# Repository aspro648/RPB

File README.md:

Rapid Prototyping Board
-------------------------------

What is it?
-----------

- Basically a 32U4 based Arduino with two card-edge slots instead of a shield layout.

Why?
----

- It started out as a 20-pin harness tester (Use Case 1), but morphed into a more generic prototyping system.
- Allows you to quickly prototype systems out on inexpensive small PCBs

Features:
---------

- USB programable Atmega 32U4.
- 20 i/o lines on card 1 position.
- Power, i2c, SPI on both card positions.
- Ability to check what card is plugged in each bay.

License
----------------
[Attribution-ShareAlike 3.0 United States (CC BY-SA 3.0 US)](https://creativecommons.org/licenses/by-sa/3.0/us/)

You are free to:

- Share — copy and redistribute the material in any medium or format
- Adapt — remix, transform, and build upon the material

Under the following terms:

- Attribution — You must give appropriate credit, provide a link to the license, and indicate if changes were made. You may do so in any reasonable manner, but not in any way that suggests the licensor endorses you or your use.
- ShareAlike — If you remix, transform, or build upon the material, you must distribute your contributions under the same license as the original.

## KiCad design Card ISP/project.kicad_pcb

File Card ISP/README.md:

Rapid Prototyping Card - ArduinoISP
---------------------------------------

What is it?
-----------

- Use RPB as an ISP programmer. 
- Sockets for Atmega8/168/328 & Attiny25/24/85.
- ISP jumper for on-board programming.
- D13 (Atmega) and D2 (Attiny) LED for troubleshooting.
- Fused to prevent reversed Attiny meltdown!

Bill Of Materials
----------------
  
- 1 ea., Perfect Purple PCB from OSH Park, https://oshpark.com/shared_projects/yUt0KZ6C
- 2 ea., C1 CAP CER 10UF 10V X5R 0805, Kemet C0805C106K8PAC7800, https://www.digikey.com/short/32v75tfv
- 2 ea., SMD LED GREEN 0603, Lite-On LTST-C191KGKT, https://www.digikey.com/short/ptwhtwz2
- 1 ea., SMD LED RED 0603, Lite-On LTST-C191KRKT, https://www.digikey.com/short/1p9dvv1t
- 1 ea., SMD LED YELLOW 0603, Lite-On LTST-C191KSKT, https://www.digikey.com/short/d20z9t1z
- 1 ea., PTC RESET FUSE 20V 54MA 0805, Murata PRG21AR420MB1RA, https://www.digikey.com/short/2nmhrbvf
- 4 ea., Resistor 1K OHM SMD 0603, Stackpole RNCP0603FTD1K00, https://www.digikey.com/short/704h9hfn
- 1 ea., CONN IC DIP SOCKET 28POS TIN, On Shore ED281DT, https://www.digikey.com/short/d8nq4rd3
- 1 ea., CONN IC DIP SOCKET 8POS, On Shore ED08DT, https://www.digikey.com/short/3tnrjzh5
- 1 ea., 6-PIN SOCKET/SOCKET IDC CABLE, Adafruit 371, https://www.digikey.com/short/b992qfbd
- 1 ea., CONN HEADER VERT 6POS 2.54MM, Amphenol 77313-118-06LF, https://www.digikey.com/short/r2d1pw4f

License
----------------
[Attribution-ShareAlike 3.0 United States (CC BY-SA 3.0 US)](https://creativecommons.org/licenses/by-sa/3.0/us/)

You are free to:

- Share — copy and redistribute the material in any medium or format
- Adapt — remix, transform, and build upon the material

Under the following terms:

- Attribution — You must give appropriate credit, provide a link to the license, and indicate if changes were made. You may do so in any reasonable manner, but not in any way that suggests the licensor endorses you or your use.
- ShareAlike — If you remix, transform, or build upon the material, you must distribute your contributions under the same license as the original.

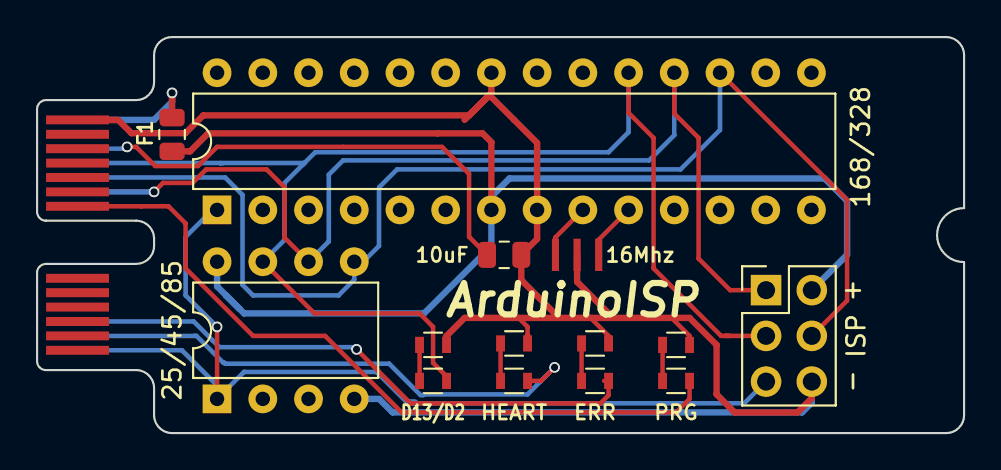
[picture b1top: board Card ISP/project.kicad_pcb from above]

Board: 2 copper layers, 51.5 x 22.0 mm, 15 parts (0 on the bottom side), 17 nets.

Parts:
C1: 10uF; C_0805_2012Metric
D1: HEART; R_0603
D2: ERR; R_0603
D3: PRG; R_0603
D4: D13/D2; R_0603
F1: 54mA; Fuse_0805_2012Metric
J1: ISP; PinHeader_2x03_P2.54mm_Vertical
R1, R2, R3, R4: 1K; R_0603
U1: 25/45/85; DIP-8_W7.62mm
U2: 168/328; DIP-28_W7.62mm
X0: Card Edge; MEC8-113-CARD_2
Y1: 16Mhz; Resonator_SMD_CTSC_1.3mmx3.2mm

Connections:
+5V: F1.2, J1.2, U1.8, U2.7
/LED_ERR: D2.2, X0.3
/LED_HB: D1.2, X0.2
/LED_PMODE: D3.2, X0.20
/MISO: J1.1, U1.6, U2.18, X0.8
/MOSI: J1.4, U1.5, U2.17, X0.9
/RESET: C1.1, X0.11
/RST: J1.5, U1.1, U2.1, X0.1
/SCK: D4.2, J1.3, U1.7, U2.19, X0.10
GND: C1.2, J1.6, R1.1, R2.1, R3.1, R4.1, U1.4, U2.8, U2.22, X0.26, Y1.2
unnamed: D1.1, R2.2
unnamed: D2.1, R3.2
unnamed: D3.1, R4.2
unnamed: D4.1, R1.2
unnamed: F1.1, X0.13
unnamed: U2.9, Y1.3
unnamed: U2.10, Y1.1

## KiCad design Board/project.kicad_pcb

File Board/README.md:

Rapid Prototyping Board
-----------------------

Bill Of Materials
----------------
  
- 1 ea., Perfect Purple PCB from OSH Park, https://oshpark.com/shared_projects/RGBCuiso
- 1 ea., U1 ATMEGA32U4-AU, IC MCU 8BIT 32KB FLASH 44TQFP, https://www.digikey.com/short/jb25pc
- 1 ea., U2 IC CURRENT MONITOR 1% 8SOIC, TI INA219AIDR, https://www.digikey.com/short/z32drn7n
- 1 ea., Y1 CER RES 16.0000MHZ 15PF SMD, Murata CSTNE16M0V530000R0, https://www.digikey.com/short/8nzcmjh3
- 2 ea., C1 CAP CER 10UF 10V X5R 0805, Kemet C0805C106K8PAC7800, https://www.digikey.com/short/32v75tfv
- 1 ea., C2 CAP CER 0.1uF 0603, https://www.digikey.com/short/h3jddqhm 
- 23 ea., D1-D23 SMD LED GREEN 0603, Lite-On LTST-C191KGKT, https://www.digikey.com/short/ptwhtwz2
- 1 ea., F1	PTC RESET FUSE 6V 500MA 0805 Eaton PTS08056V050, https://www.digikey.com/short/4182mdqq
- 2 ea., RV1, RV2 VARISTOR 10.8V 30A 0603, KYOCERA VCUG060050L1DP, https://www.digikey.com/short/0479hw0m
- 23 ea., R1-R23 Resistor 1K OHM SMD 0603, Stackpole RNCP0603FTD1K00, https://www.digikey.com/short/704h9hfn
- 2 ea., R24, R25 Resistor 22 OHM SMD 0603, Yageo RC0603JR-0722RL, https://www.digikey.com/short/93jrm3t2
- 1 ea., R26 Resistor 1M OHM SMD 0603 Yageo RC0603JR-071ML, https://www.digikey.com/short/z0jnrwbq
- 2 ea., R27, R28 Resistor 4K7 OHM SMD 0603, https://www.digikey.com/short/t89ptvpw
- 1 ea., R29 RES 0.1 OHM 1% 1W 1206, VSRP1206S1-R100F, https://www.digikey.com/short/dzw3vt1h
- 2 ea., SW1 SWITCH TACTILE SPST-NO 0.05A 12V, Wurth 434121025816, https://www.digikey.com/short/qbm0p0c9
- 1 ea., J1 CONN RCPT MICRO USB R/A SMD, Molex 1050170001, https://www.digikey.com/short/jb2205
- 2 ea., X1, X2 CONN EDGE DUAL FMALE 20POS, Samtek MEC8-113-02-L-D-RA1, https://www.digikey.com/short/50wdhmp0
- 2 ea., ROUND STANDOFF M2.5 STEEL 2.7MM, Wurth 9774027151R, https://www.digikey.com/short/47zwt3m4
- 1 ea., LED1 3535 RGB LED,  IN-PI33TBTPRPGPB https://www.digikey.com/short/qf2t8bqj
- 4 ea., BUMPER CYLINDRICAL 0.25" DIA CLR, https://www.digikey.com/short/23cbvbh5
- 2 ea., M2.5 thumbscrew https://www.mcmaster.com/99607A263/ or
		 https://www.amazon.com/CNBTR-M2-5x6mm-Knurled-Threaded-Fastener/dp/B07ZJFGGTD

Card:
- 1 ea., RPB Card 2.54mm Pitch, https://oshpark.com/shared_projects/RnMvuNFo
- 1 ea., RES 10K OHM 5% 1/10W 0603, https://www.digikey.com/short/h4w9vtd1
- 1 ea., IC EEPROM 32KBIT I2C, Microchip 24LC32AT-I/MC, https://www.digikey.com/short/r3f225vm
- 1 ea., I2C Display Module 0.91 Inch I2C, https://www.amazon.com/Pieces-Display-Module-SSD1306-Screen/dp/B08N6N8L5Q

Stencil & Jig:
- https://www.oshstencils.com/#invoice/5585b4301f5fdfe7690882e8abfac3aeba5187

License
----------------
[Attribution-ShareAlike 3.0 United States (CC BY-SA 3.0 US)](https://creativecommons.org/licenses/by-sa/3.0/us/)

You are free to:

- Share — copy and redistribute the material in any medium or format
- Adapt — remix, transform, and build upon the material

Under the following terms:

- Attribution — You must give appropriate credit, provide a link to the license, and indicate if changes were made. You may do so in any reasonable manner, but not in any way that suggests the licensor endorses you or your use.
- ShareAlike — If you remix, transform, or build upon the material, you must distribute your contributions under the same license as the original.

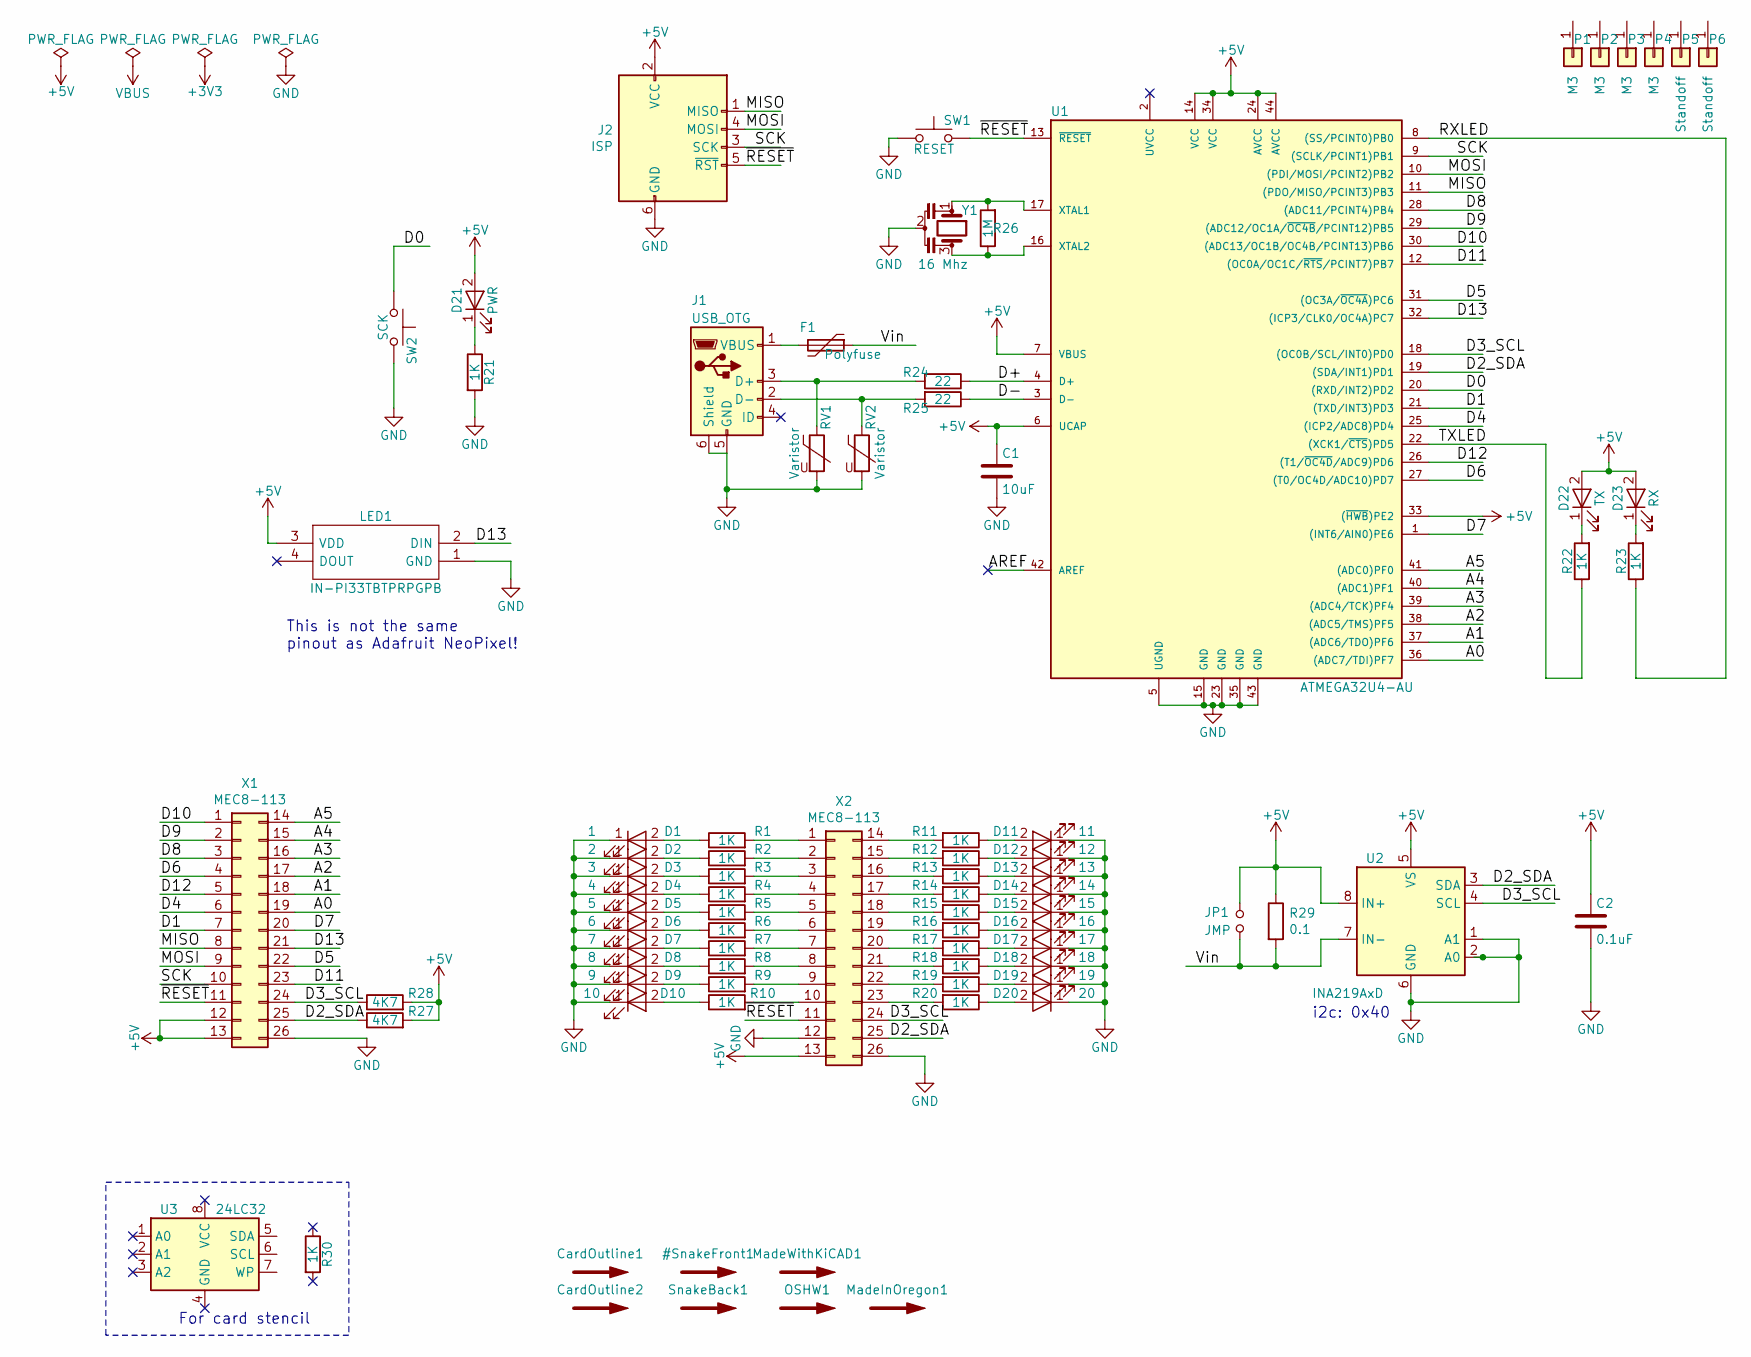
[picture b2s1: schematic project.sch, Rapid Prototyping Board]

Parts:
C1: 10uF; C_0805
C2: 0.1uF; C_0603
CardOutline1, CardOutline2: SYM_Arrow_Large; MEC8-113-CARD_2outline
D1: 1; LED_0603
D2: 2; LED_0603
D3: 3; LED_0603
D4: 4; LED_0603
D5: 5; LED_0603
D6: 6; LED_0603
D7: 7; LED_0603
D8: 8; LED_0603
D9: 9; LED_0603
D10: 10; LED_0603
D11: 11; LED_0603
D12: 12; LED_0603
D13: 13; LED_0603
D14: 14; LED_0603
D15: 15; LED_0603
D16: 16; LED_0603
D17: 17; LED_0603
D18: 18; LED_0603
D19: 19; LED_0603
D20: 20; LED_0603
D21: PWR; LED_0603
D22: TX; LED_0603
D23: RX; LED_0603
F1: Polyfuse; R_0805_HandSoldering
J1: USB_OTG; USB_Micro-B_Molex-105017-0001
J2: ISP; Pin_Header_Straight_2x03_Pitch2.54mm
JP1: JMP; Jumper
LED1: IN-PI33TBTPRPGPB; INPI33TBTPRPGPB; Mouser Part Number 743-IN-PI33TBTPRPGPB
MadeInOregon1: SYM_Arrow_Large; MadeInOregonRev25
MadeWithKiCAD1: SYM_Arrow_Large; KiCad-Logo2_8mm_SilkScreen
OSHW1: SYM_Arrow_Large; OSHW-Logo_11.4x12mm_SilkScreen
P1, P2, P3, P4: M3; M3mount
P5, P6: Standoff; M25standoff
R1, R2, R3, R4, R5, R6, R7, R8, R9, R10, R11, R12, R13, R14, R15, R16, R17, R18, R19, R20, R21, R22, R23, R30: 1K; R_0603
R24, R25: 22; R_0603
R26: 1M; R_0603
R27, R28: 4K7; R_0603
R29: 0.1; R_1206
RV1, RV2: Varistor; R_0603
SW1: RESET; SW_TS10-63-26-BE-250-SMT-TR
SW2: SCK; SW_TS10-63-26-BE-250-SMT-TR
SnakeBack1: SYM_Arrow_Large; Snake
U1: ATMEGA32U4-AU; TQFP-44_10x10mm_Pitch0.8mm
U2: INA219AxD; SOIC-8_3.9x4.9mm_P1.27mm
U3: 24LC32; DFN-8-1EP_3x2mm
X1, X2: MEC8-113; SAMTEC_MEC8-113-TOP-BOTTOM
Y1: 16 Mhz; Resonator_SMD_CTSC_1.3mmx3.2mm

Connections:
+5V: C1.1, C2.1, D21.2 (A), D22.2 (A), D23.2 (A), J2.2 (VCC), JP1.1, LED1.3 (VDD), R27.2, R28.2, R29.1, U1.6 (UCAP), U1.7 (VBUS), U1.14 (VCC), U1.24 (AVCC), U1.33 ((~HWB~)PE2), U1.34 (VCC), U1.44 (AVCC), U2.5 (VS), U2.8 (IN+), X1.12, X1.13, X2.13
/A0: U1.36 ((ADC7/TDI)PF7), X1.19
/A1: U1.37 ((ADC6/TDO)PF6), X1.18
/A2: U1.38 ((ADC5/TMS)PF5), X1.17
/A3: U1.39 ((ADC4/TCK)PF4), X1.16
/A4: U1.40 ((ADC1)PF1), X1.15
/A5: U1.41 ((ADC0)PF0), X1.14
/D0: SW2.1, U1.20 ((RXD/INT2)PD2)
/D1: U1.21 ((TXD/INT3)PD3), X1.7
/D2_SDA: R27.1, U1.19 ((SDA/INT1)PD1), U2.3 (SDA), X1.25, X2.25
/D3_SCL: R28.1, U1.18 ((OC0B/SCL/INT0)PD0), U2.4 (SCL), X1.24, X2.24
/D4: U1.25 ((ICP2/ADC8)PD4), X1.6
/D5: U1.31 ((OC3A/~OC4A~)PC6), X1.22
/D6: U1.27 ((T0/OC4D/ADC10)PD7), X1.4
/D7: U1.1 ((INT6/AIN0)PE6), X1.20
/D8: U1.28 ((ADC11/PCINT4)PB4), X1.3
/D9: U1.29 ((ADC12/OC1A/~OC4B~/PCINT12)PB5), X1.2
/D10: U1.30 ((ADC13/OC1B/OC4B/PCINT13)PB6), X1.1
/D11: U1.12 ((OC0A/OC1C/~RTS~/PCINT7)PB7), X1.23
/D12: U1.26 ((T1/~OC4D~/ADC9)PD6), X1.5
/D13: LED1.2 (DIN), U1.32 ((ICP3/CLK0/OC4A)PC7), X1.21
/D+: R24.1, U1.4 (D+)
/D-: R25.1, U1.3 (D-)
/MISO: J2.1 (MISO), U1.11 ((PDO/MISO/PCINT3)PB3), X1.8
/MOSI: J2.4 (MOSI), U1.10 ((PDI/MOSI/PCINT2)PB2), X1.9
/RXLED: R23.1, U1.8 ((SS/PCINT0)PB0)
/SCK: J2.3 (SCK), U1.9 ((SCLK/PCINT1)PB1), X1.10
/TXLED: R22.1, U1.22 ((XCK1/~CTS~)PD5)
/Vin: F1.1, JP1.2, R29.2, U2.7 (IN-)
/~RESET: J2.5 (~RST), SW1.2, U1.13 (~RESET~), X1.11, X2.11
GND: C1.2, C2.2, D1.1 (K), D2.1 (K), D3.1 (K), D4.1 (K), D5.1 (K), D6.1 (K), D7.1 (K), D8.1 (K), D9.1 (K), D10.1 (K), D11.1 (K), D12.1 (K), D13.1 (K), D14.1 (K), D15.1 (K), D16.1 (K), D17.1 (K), D18.1 (K), D19.1 (K), D20.1 (K), J1.5 (GND), J1.6 (Shield), J2.6 (GND), LED1.1 (GND), R21.2, RV1.2, RV2.2, SW1.1, SW2.2, U1.5 (UGND), U1.15 (GND), U1.23 (GND), U1.35 (GND), U1.43 (GND), U2.1 (A1), U2.2 (A0), U2.6 (GND), X1.26, X2.12, X2.26, Y1.2
unnamed: D1.2 (A), R1.1
unnamed: D2.2 (A), R2.1
unnamed: D3.2 (A), R3.1
unnamed: D4.2 (A), R4.1
unnamed: D5.2 (A), R5.1
unnamed: D6.2 (A), R6.1
unnamed: D7.2 (A), R7.1
unnamed: D8.2 (A), R8.1
unnamed: D9.2 (A), R9.1
unnamed: D10.2 (A), R10.1
unnamed: D11.2 (A), R11.1
unnamed: D12.2 (A), R12.1
unnamed: D13.2 (A), R13.1
unnamed: D14.2 (A), R14.1
unnamed: D15.2 (A), R15.1
unnamed: D16.2 (A), R16.1
unnamed: D17.2 (A), R17.1
unnamed: D18.2 (A), R18.1
unnamed: D19.2 (A), R19.1
unnamed: D20.2 (A), R20.1
unnamed: D21.1 (K), R21.1
unnamed: D22.1 (K), R22.2
unnamed: D23.1 (K), R23.2
unnamed: F1.2, J1.1 (VBUS)
unnamed: J1.2 (D-), R25.2, RV2.1
unnamed: J1.3 (D+), R24.2, RV1.1
unnamed: R1.2, X2.1
unnamed: R2.2, X2.2
unnamed: R3.2, X2.3
unnamed: R4.2, X2.4
unnamed: R5.2, X2.5
unnamed: R6.2, X2.6
unnamed: R7.2, X2.7
unnamed: R8.2, X2.8
unnamed: R9.2, X2.9
unnamed: R10.2, X2.10
unnamed: R11.2, X2.14
unnamed: R12.2, X2.15
unnamed: R13.2, X2.16
unnamed: R14.2, X2.17
unnamed: R15.2, X2.18
unnamed: R16.2, X2.19
unnamed: R17.2, X2.20
unnamed: R18.2, X2.21
unnamed: R19.2, X2.22
unnamed: R20.2, X2.23
unnamed: R26.1, U1.16 (XTAL2), Y1.3
unnamed: R26.2, U1.17 (XTAL1), Y1.1

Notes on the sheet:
This is not the same pinout as Adafruit NeoPixel!
i2c: 0x40
For card stencil

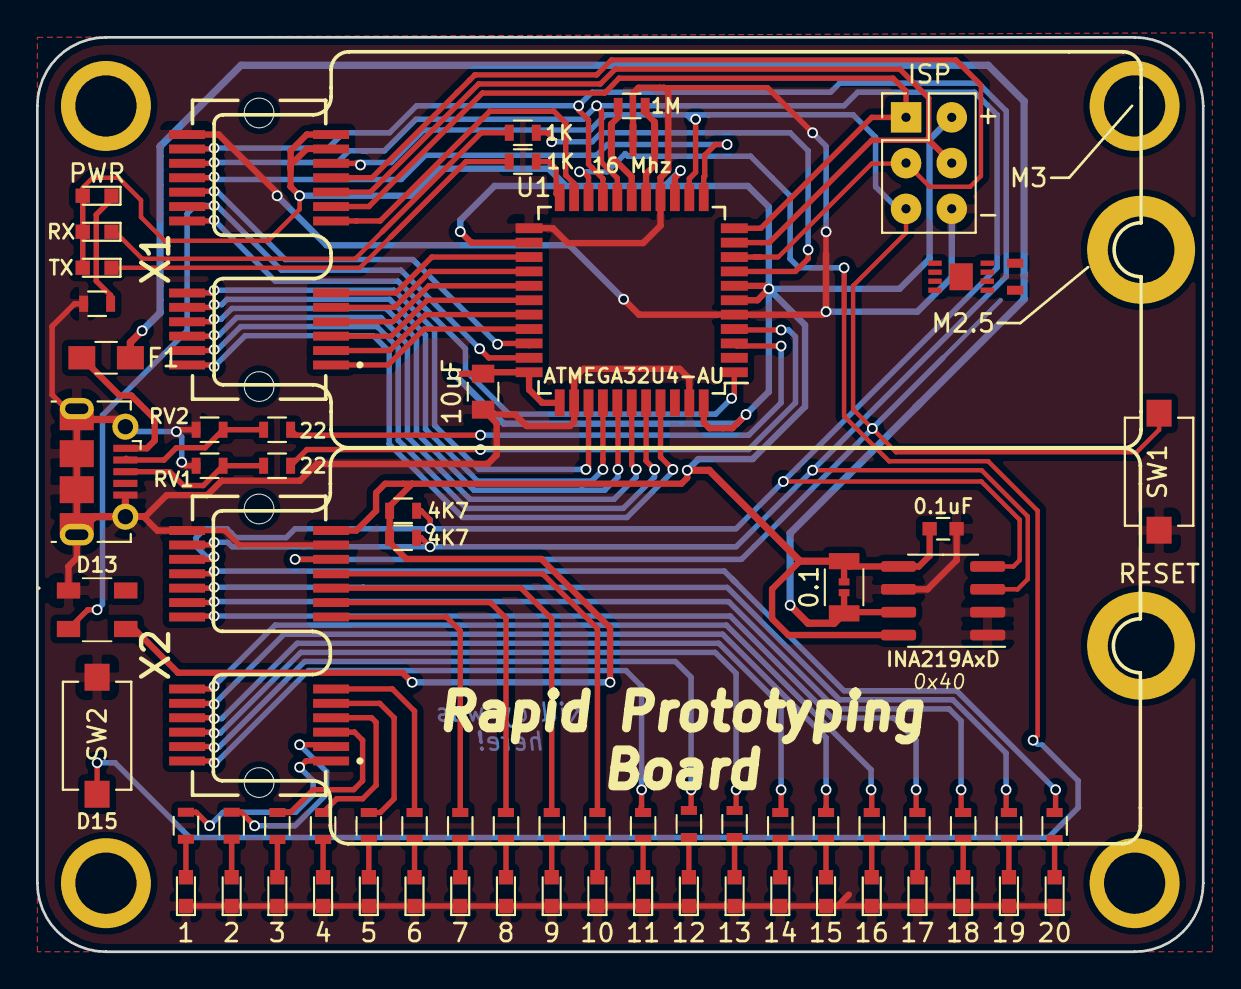
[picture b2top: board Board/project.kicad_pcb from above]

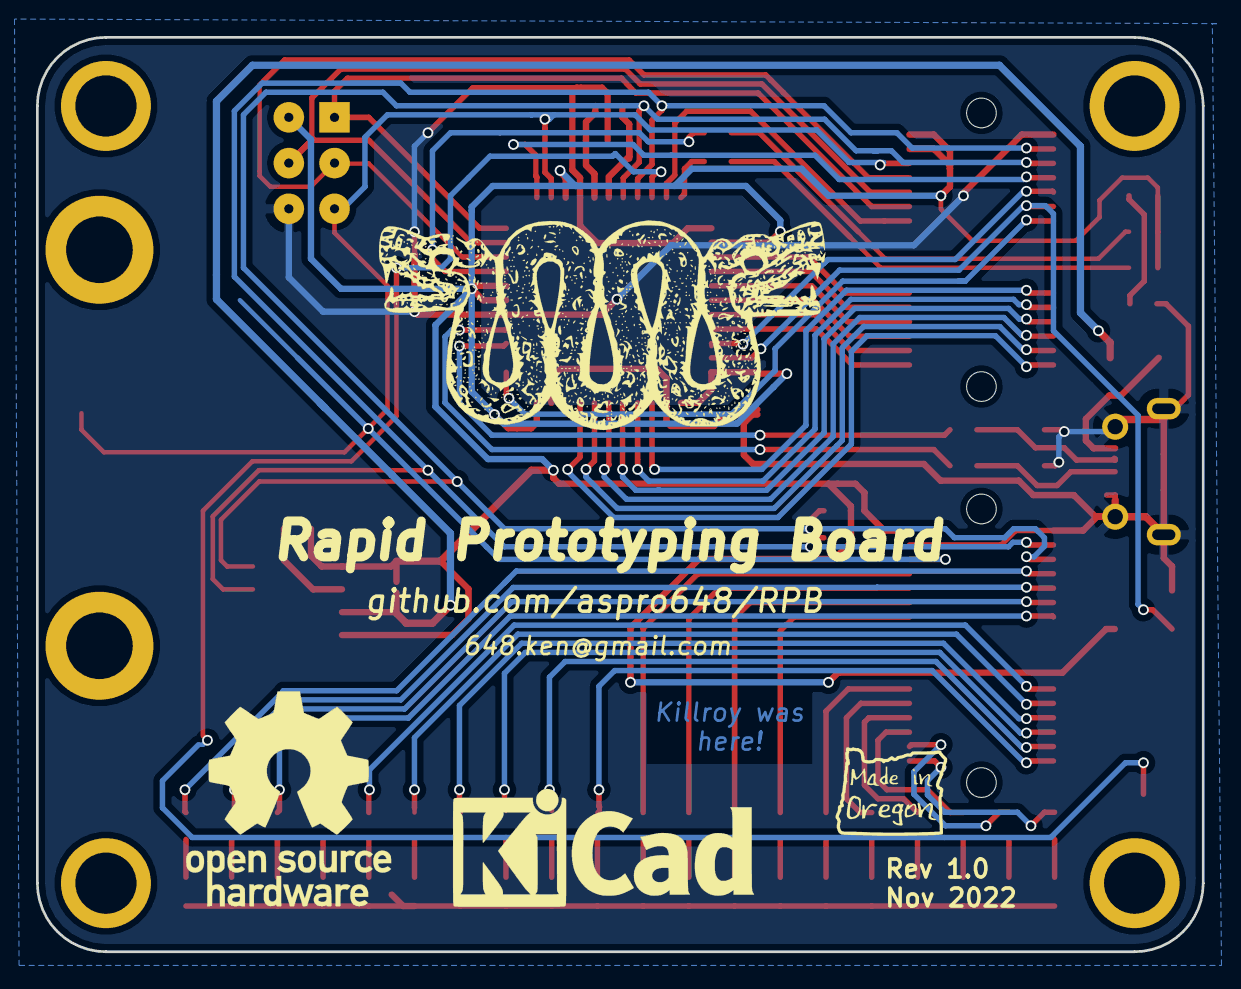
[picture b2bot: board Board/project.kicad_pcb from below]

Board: 2 copper layers, 64.8 x 50.8 mm, 82 parts (3 on the bottom side), 79 nets.

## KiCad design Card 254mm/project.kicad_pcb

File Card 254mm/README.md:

Rapid Prototyping Card - 2.54mm Pitch
-------------------------------------

Bill Of Materials
----------------
  
- PCB from KiCad project.kicad_pcb file  
- 1 ea., RES 10K OHM 5% 1/10W 0603, https://www.digikey.com/short/h4w9vtd1
- 1 ea., IC EEPROM 32KBIT I2C, Microchip 24LC32AT-I/MC, https://www.digikey.com/short/r3f225vm

License
----------------
[Attribution-ShareAlike 3.0 United States (CC BY-SA 3.0 US)](https://creativecommons.org/licenses/by-sa/3.0/us/)

You are free to:

- Share — copy and redistribute the material in any medium or format
- Adapt — remix, transform, and build upon the material

Under the following terms:

- Attribution — You must give appropriate credit, provide a link to the license, and indicate if changes were made. You may do so in any reasonable manner, but not in any way that suggests the licensor endorses you or your use.
- ShareAlike — If you remix, transform, or build upon the material, you must distribute your contributions under the same license as the original.

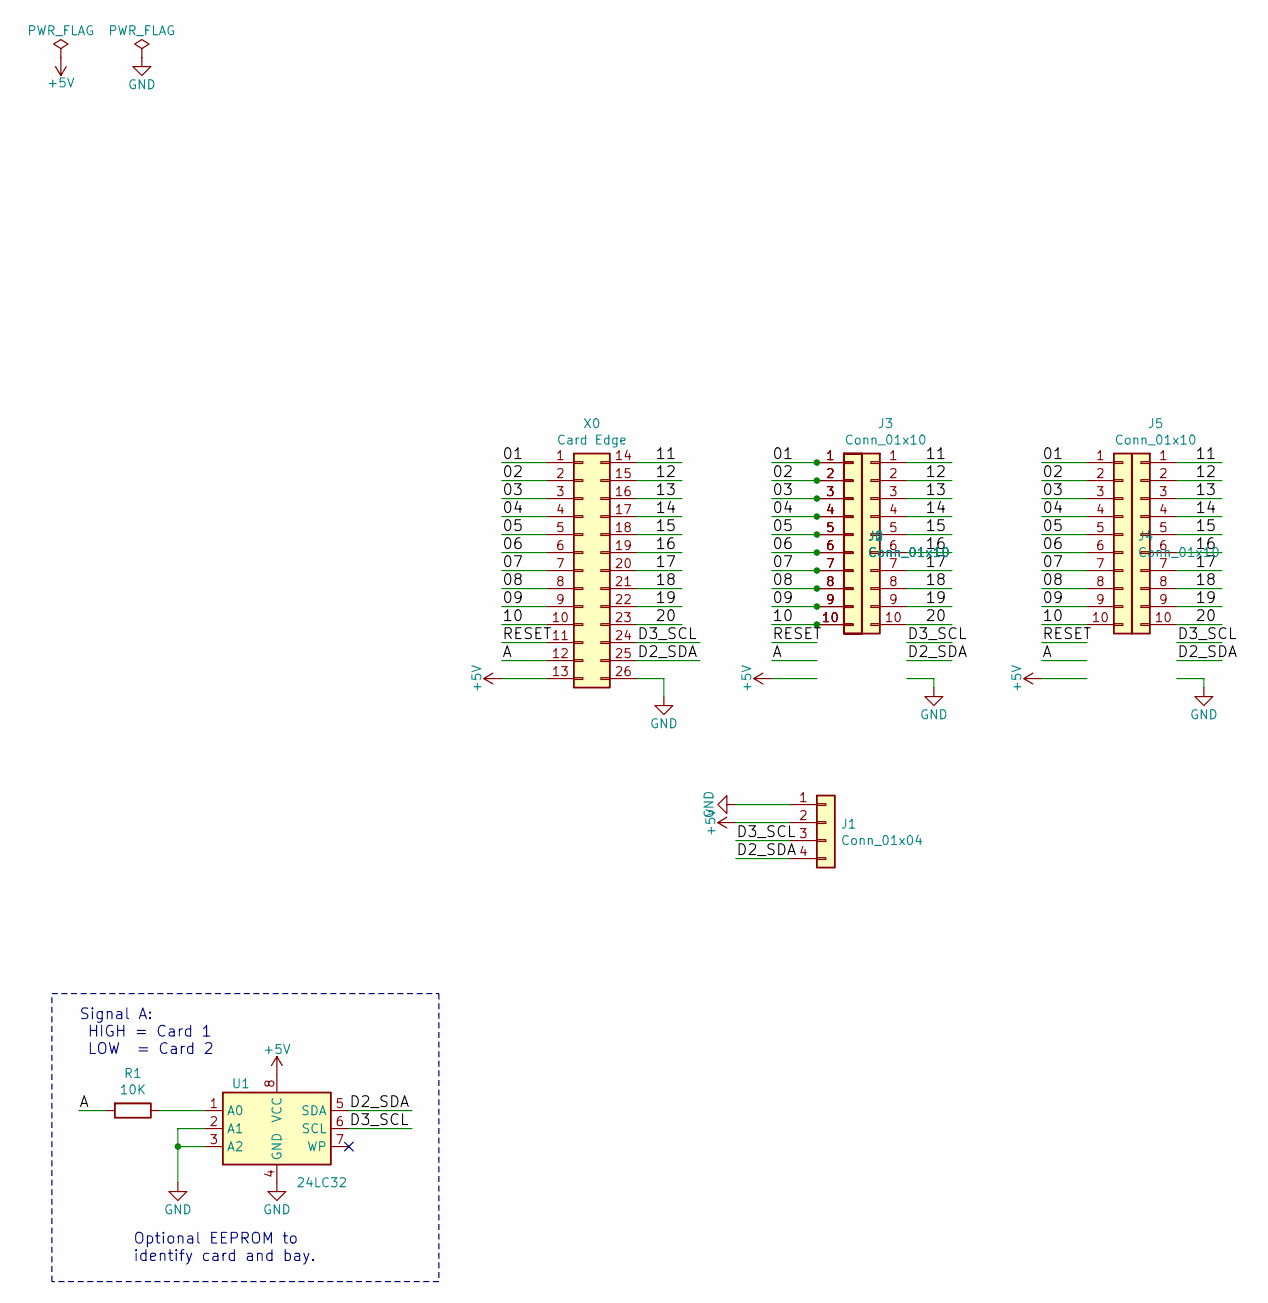
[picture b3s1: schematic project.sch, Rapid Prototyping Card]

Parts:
J1: Conn_01x04; PinHeader_1x04_P2.54mm_Vertical
J2, J3, J4, J5, J6: Conn_01x10; PinHeader_1x10_P2.54mm_Vertical
R1: 10K; R_0603
U1: 24LC32; DFN-8-1EP_3x2mm
X0: Card Edge; MEC8-113-CARD_2

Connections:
+5V: J1.2, U1.8 (VCC), X0.13
/01: J2.1, J4.1, J6.1, X0.1
/02: J2.2, J4.2, J6.2, X0.2
/03: J2.3, J4.3, J6.3, X0.3
/04: J2.4, J4.4, J6.4, X0.4
/05: J2.5, J4.5, J6.5, X0.5
/06: J2.6, J4.6, J6.6, X0.6
/07: J2.7, J4.7, J6.7, X0.7
/08: J2.8, J4.8, J6.8, X0.8
/09: J2.9, J4.9, J6.9, X0.9
/10: J2.10, J4.10, J6.10, X0.10
/11: J3.1, J5.1, X0.14
/12: J3.2, J5.2, X0.15
/13: J3.3, J5.3, X0.16
/14: J3.4, J5.4, X0.17
/15: J3.5, J5.5, X0.18
/16: J3.6, J5.6, X0.19
/17: J3.7, J5.7, X0.20
/18: J3.8, J5.8, X0.21
/19: J3.9, J5.9, X0.22
/20: J3.10, J5.10, X0.23
/A: R1.2, X0.12
/D2_SDA: J1.4, U1.5 (SDA), X0.25
/D3_SCL: J1.3, U1.6 (SCL), X0.24
GND: J1.1, U1.2 (A1), U1.3 (A2), U1.4 (GND), X0.26
unnamed: R1.1, U1.1 (A0)

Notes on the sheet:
Signal A: HIGH = Card 1 LOW = Card 2
Optional EEPROM to identify card and bay.

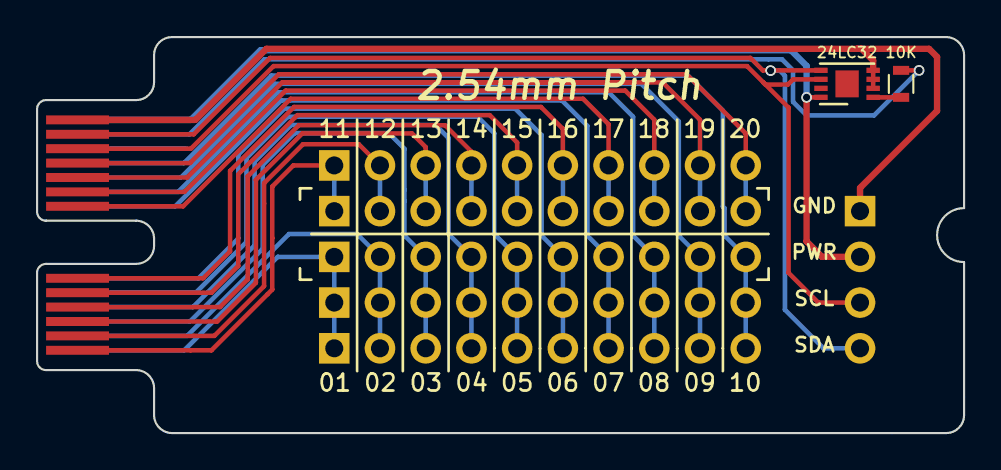
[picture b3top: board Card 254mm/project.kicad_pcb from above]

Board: 2 copper layers, 51.5 x 22.0 mm, 9 parts (0 on the bottom side), 26 nets.

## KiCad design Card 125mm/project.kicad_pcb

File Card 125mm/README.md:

Rapid Prototyping Card - 1.25mm Pitch
-------------------------------------

Bill Of Materials
----------------
  
- PCB from KiCad project.kicad_pcb file  
- 1 ea., RES 10K OHM 5% 1/10W 0603, https://www.digikey.com/short/h4w9vtd1
- 1 ea., IC EEPROM 32KBIT I2C, Microchip 24LC32AT-I/MC, https://www.digikey.com/short/r3f225vm
- 1 ea., CONN HEADER VERT 10POS 1.25MM, Molex 0530471010, https://www.digikey.com/short/jfwfhm5n
- 1 ea., CONN HEADER VERT 10POS 1.25MM, Hirose DF13-10P-1.25DSA, https://www.digikey.com/short/f5pm7mt2

License
----------------
[Attribution-ShareAlike 3.0 United States (CC BY-SA 3.0 US)](https://creativecommons.org/licenses/by-sa/3.0/us/)

You are free to:

- Share — copy and redistribute the material in any medium or format
- Adapt — remix, transform, and build upon the material

Under the following terms:

- Attribution — You must give appropriate credit, provide a link to the license, and indicate if changes were made. You may do so in any reasonable manner, but not in any way that suggests the licensor endorses you or your use.
- ShareAlike — If you remix, transform, or build upon the material, you must distribute your contributions under the same license as the original.

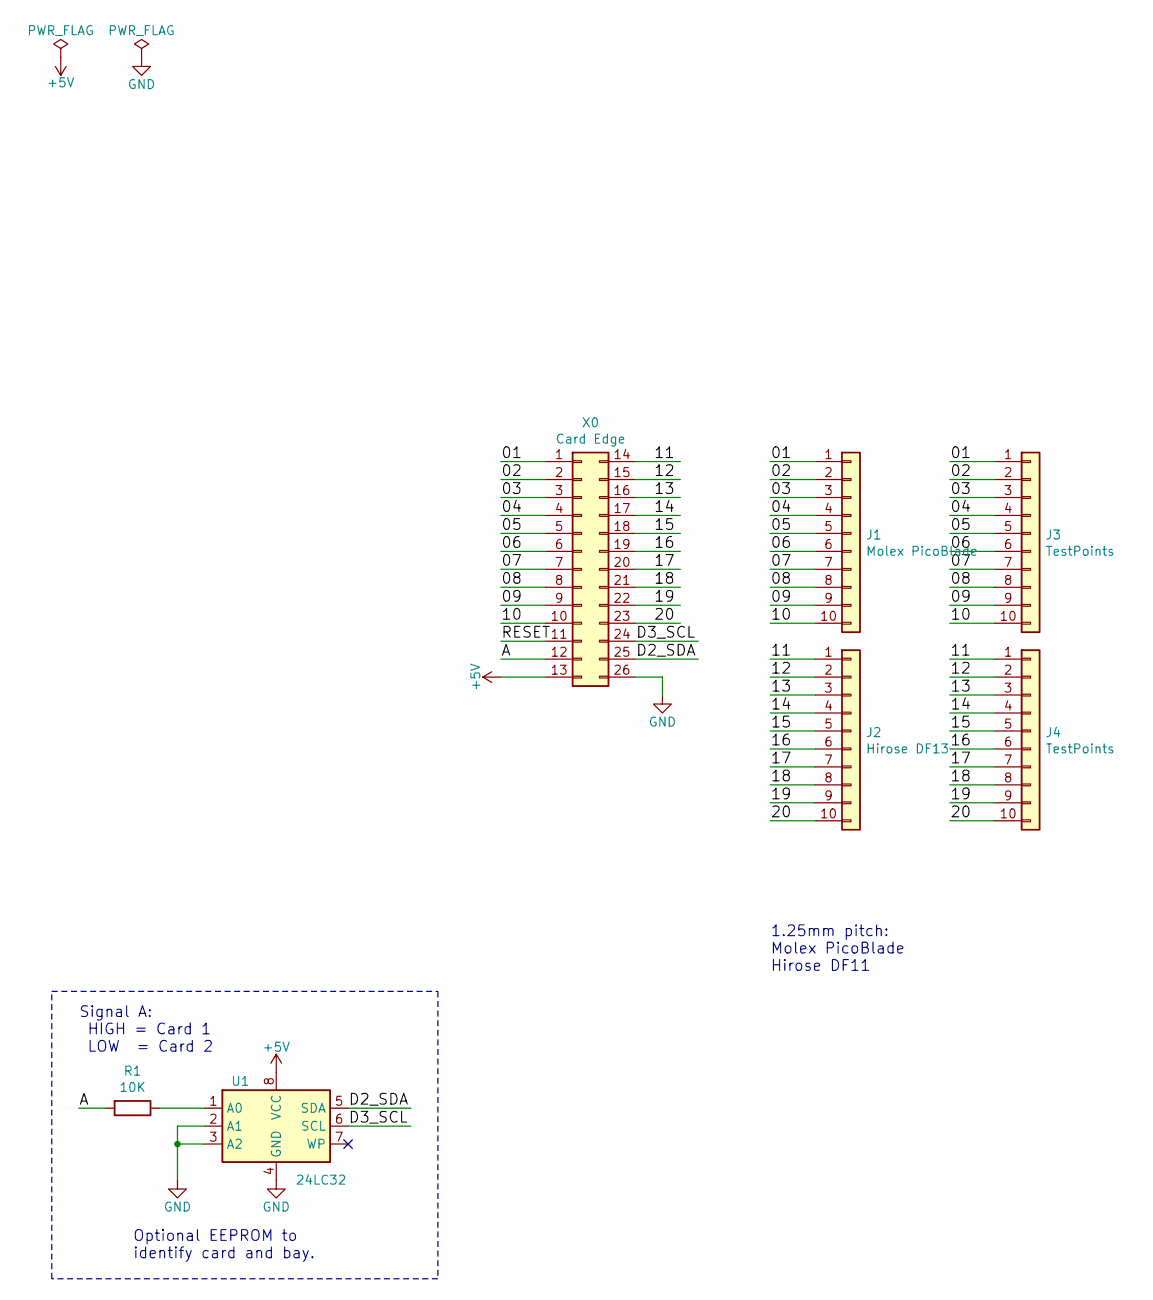
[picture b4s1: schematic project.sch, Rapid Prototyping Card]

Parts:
J1: Molex PicoBlade; Molex_PicoBlade_53047-1010_1x10_P1.25mm_Vertical
J2: Hirose DF13; Hirose_DF13-10P-1.25DSA_1x10_P1.25mm_Vertical
J3, J4: TestPoints; TestPoints_1x10_P1.25mm_Vertical
R1: 10K; R_0603
U1: 24LC32; DFN-8-1EP_2x3mm_P0.5mm_EP0.61x2.2mm
X0: Card Edge; MEC8-113-CARD_2

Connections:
+5V: U1.8 (VCC), X0.13
/01: J1.1, J3.1, X0.1
/02: J1.2, J3.2, X0.2
/03: J1.3, J3.3, X0.3
/04: J1.4, J3.4, X0.4
/05: J1.5, J3.5, X0.5
/06: J1.6, J3.6, X0.6
/07: J1.7, J3.7, X0.7
/08: J1.8, J3.8, X0.8
/09: J1.9, J3.9, X0.9
/10: J1.10, J3.10, X0.10
/11: J2.1, J4.1, X0.14
/12: J2.2, J4.2, X0.15
/13: J2.3, J4.3, X0.16
/14: J2.4, J4.4, X0.17
/15: J2.5, J4.5, X0.18
/16: J2.6, J4.6, X0.19
/17: J2.7, J4.7, X0.20
/18: J2.8, J4.8, X0.21
/19: J2.9, J4.9, X0.22
/20: J2.10, J4.10, X0.23
/A: R1.2, X0.12
/D2_SDA: U1.5 (SDA), X0.25
/D3_SCL: U1.6 (SCL), X0.24
GND: U1.2 (A1), U1.3 (A2), U1.4 (GND), X0.26
unnamed: R1.1, U1.1 (A0)

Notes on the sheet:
Signal A: HIGH = Card 1 LOW = Card 2
Optional EEPROM to identify card and bay.
1.25mm pitch: Molex PicoBlade Hirose DF11

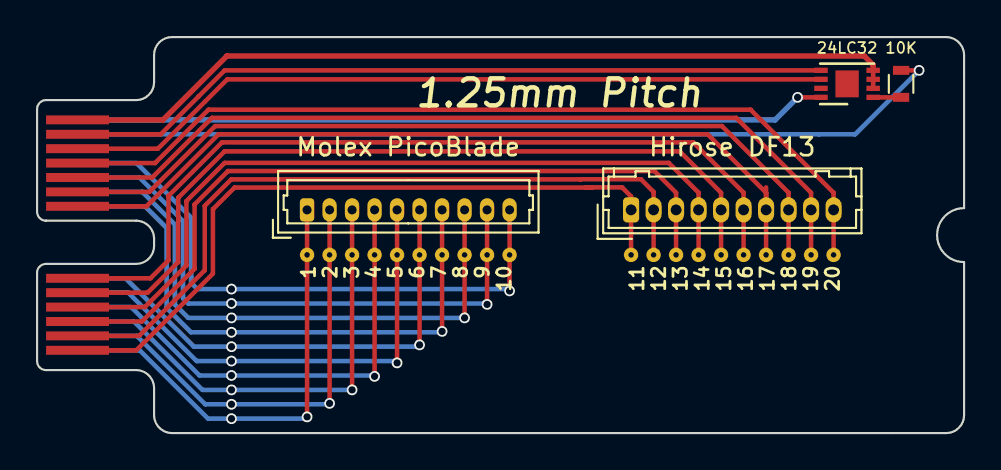
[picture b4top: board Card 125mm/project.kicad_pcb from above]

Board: 2 copper layers, 51.5 x 22.0 mm, 7 parts (0 on the bottom side), 26 nets.

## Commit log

2022-12-01 EEPROM footprint update
